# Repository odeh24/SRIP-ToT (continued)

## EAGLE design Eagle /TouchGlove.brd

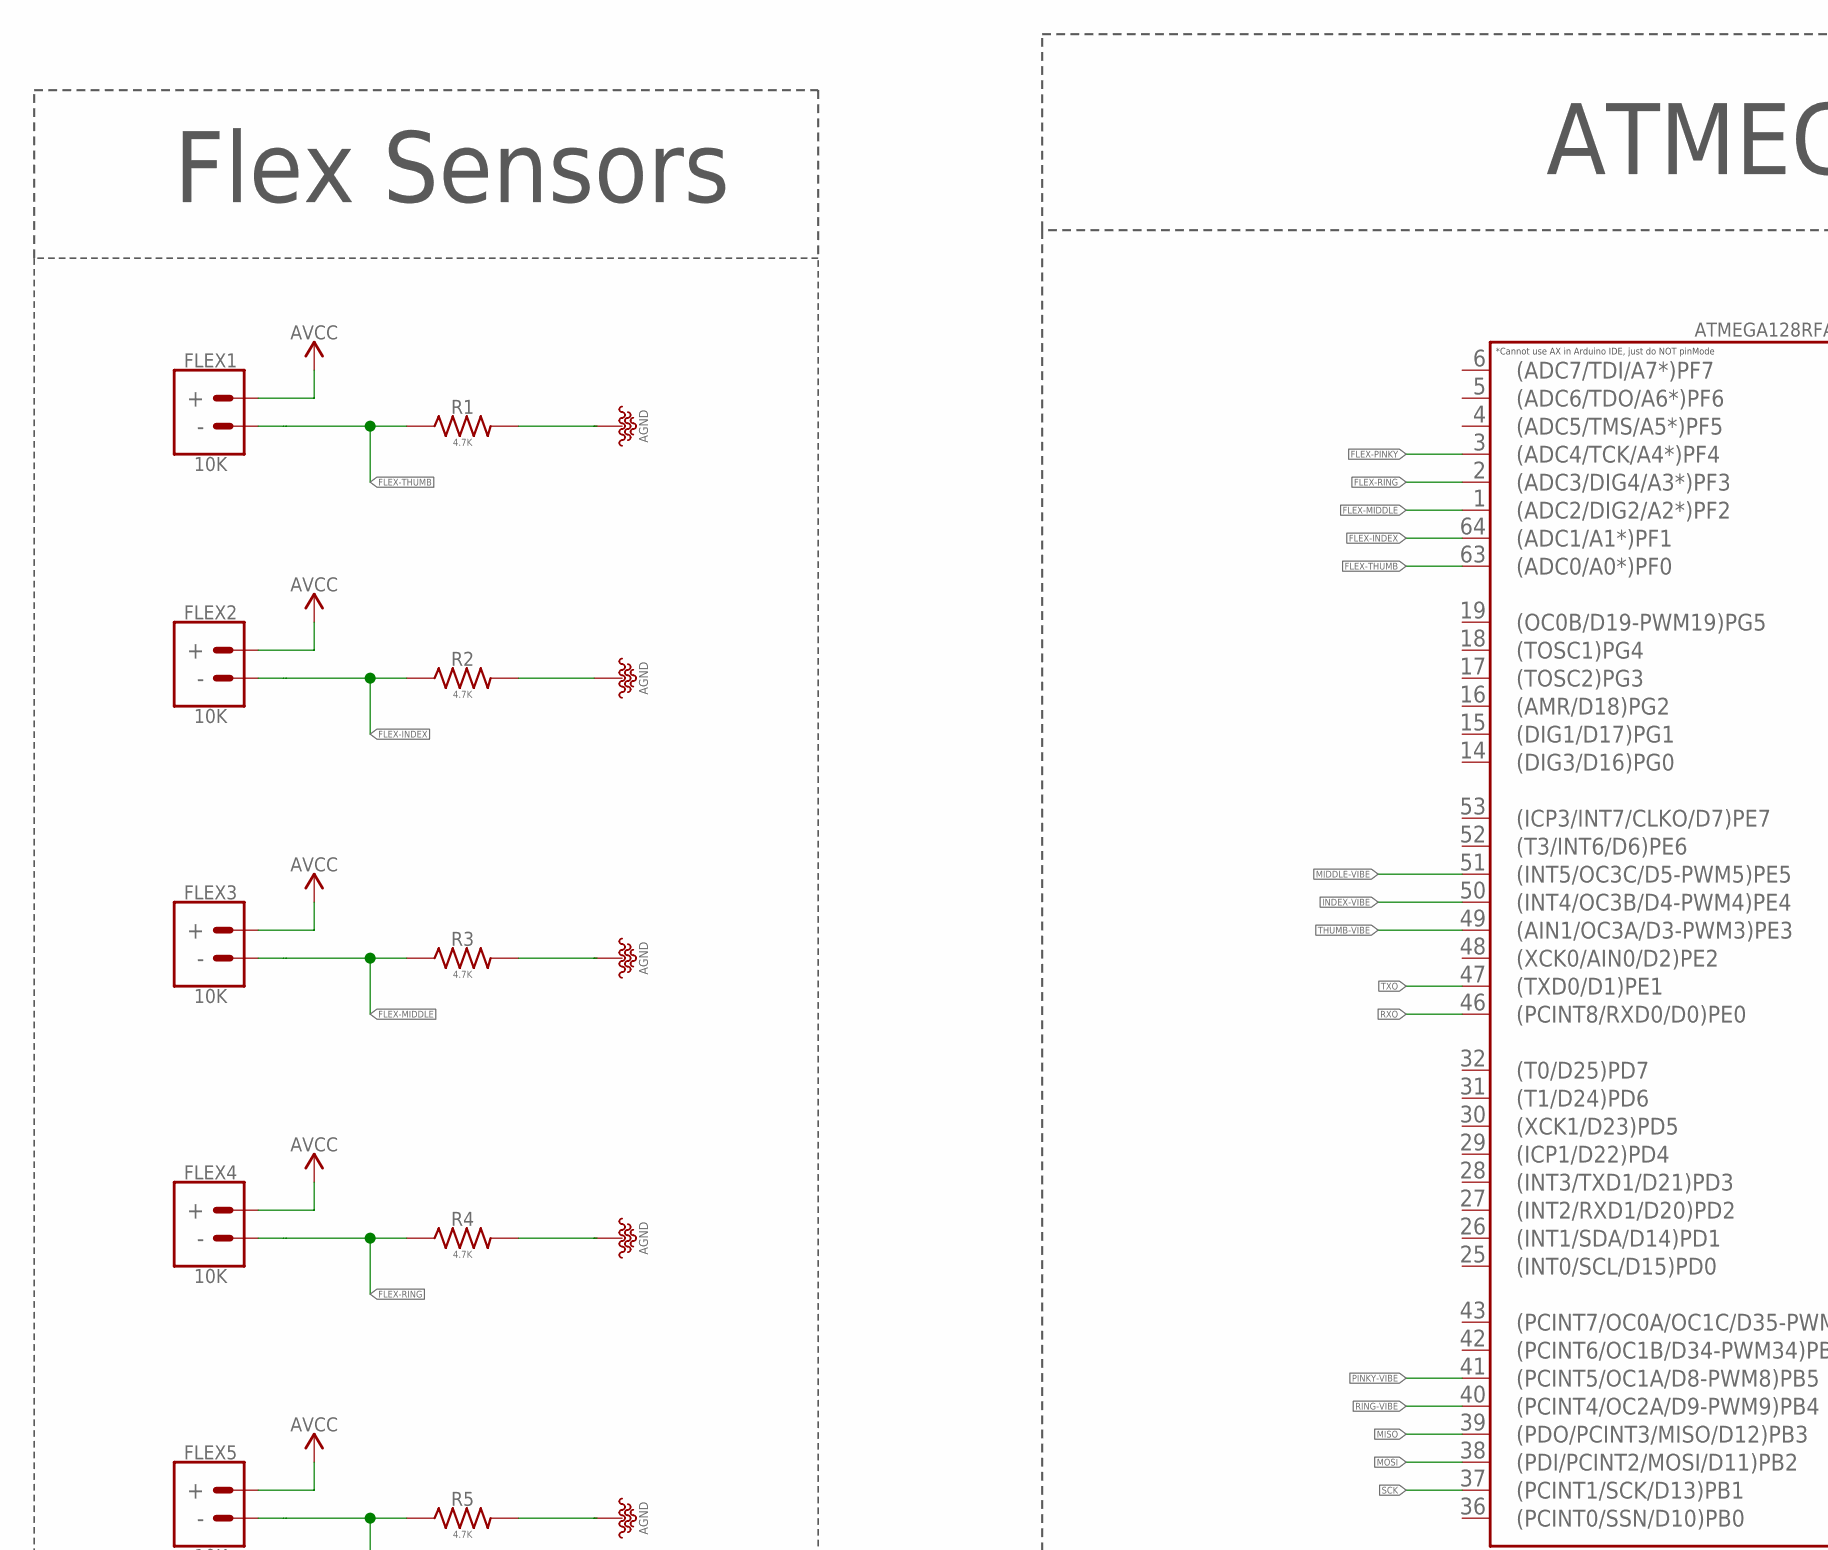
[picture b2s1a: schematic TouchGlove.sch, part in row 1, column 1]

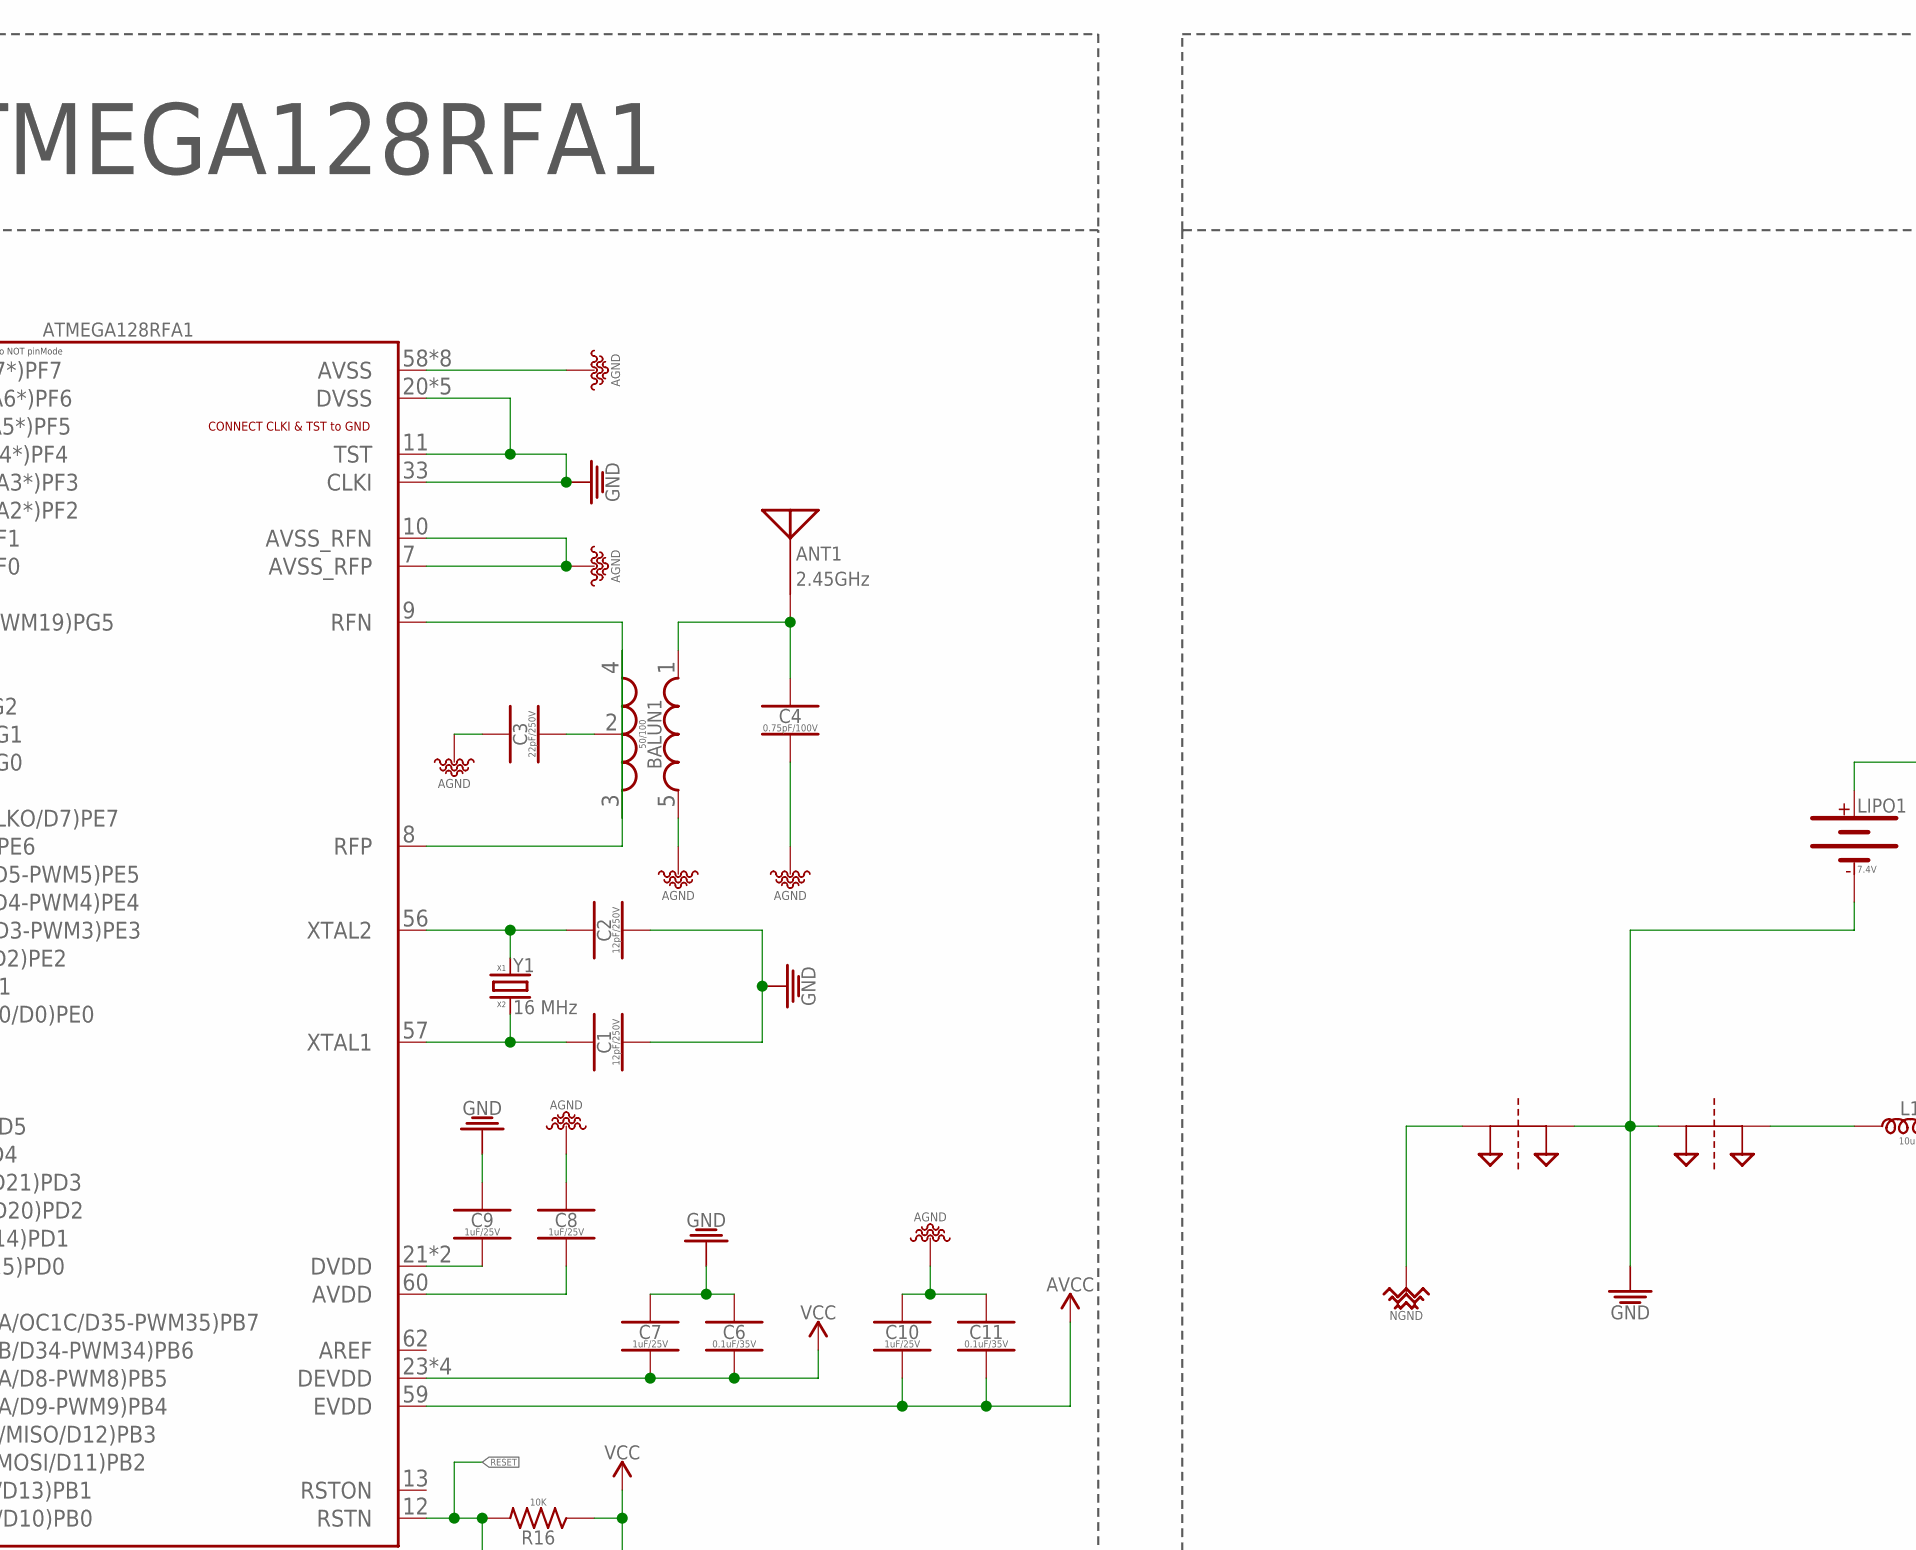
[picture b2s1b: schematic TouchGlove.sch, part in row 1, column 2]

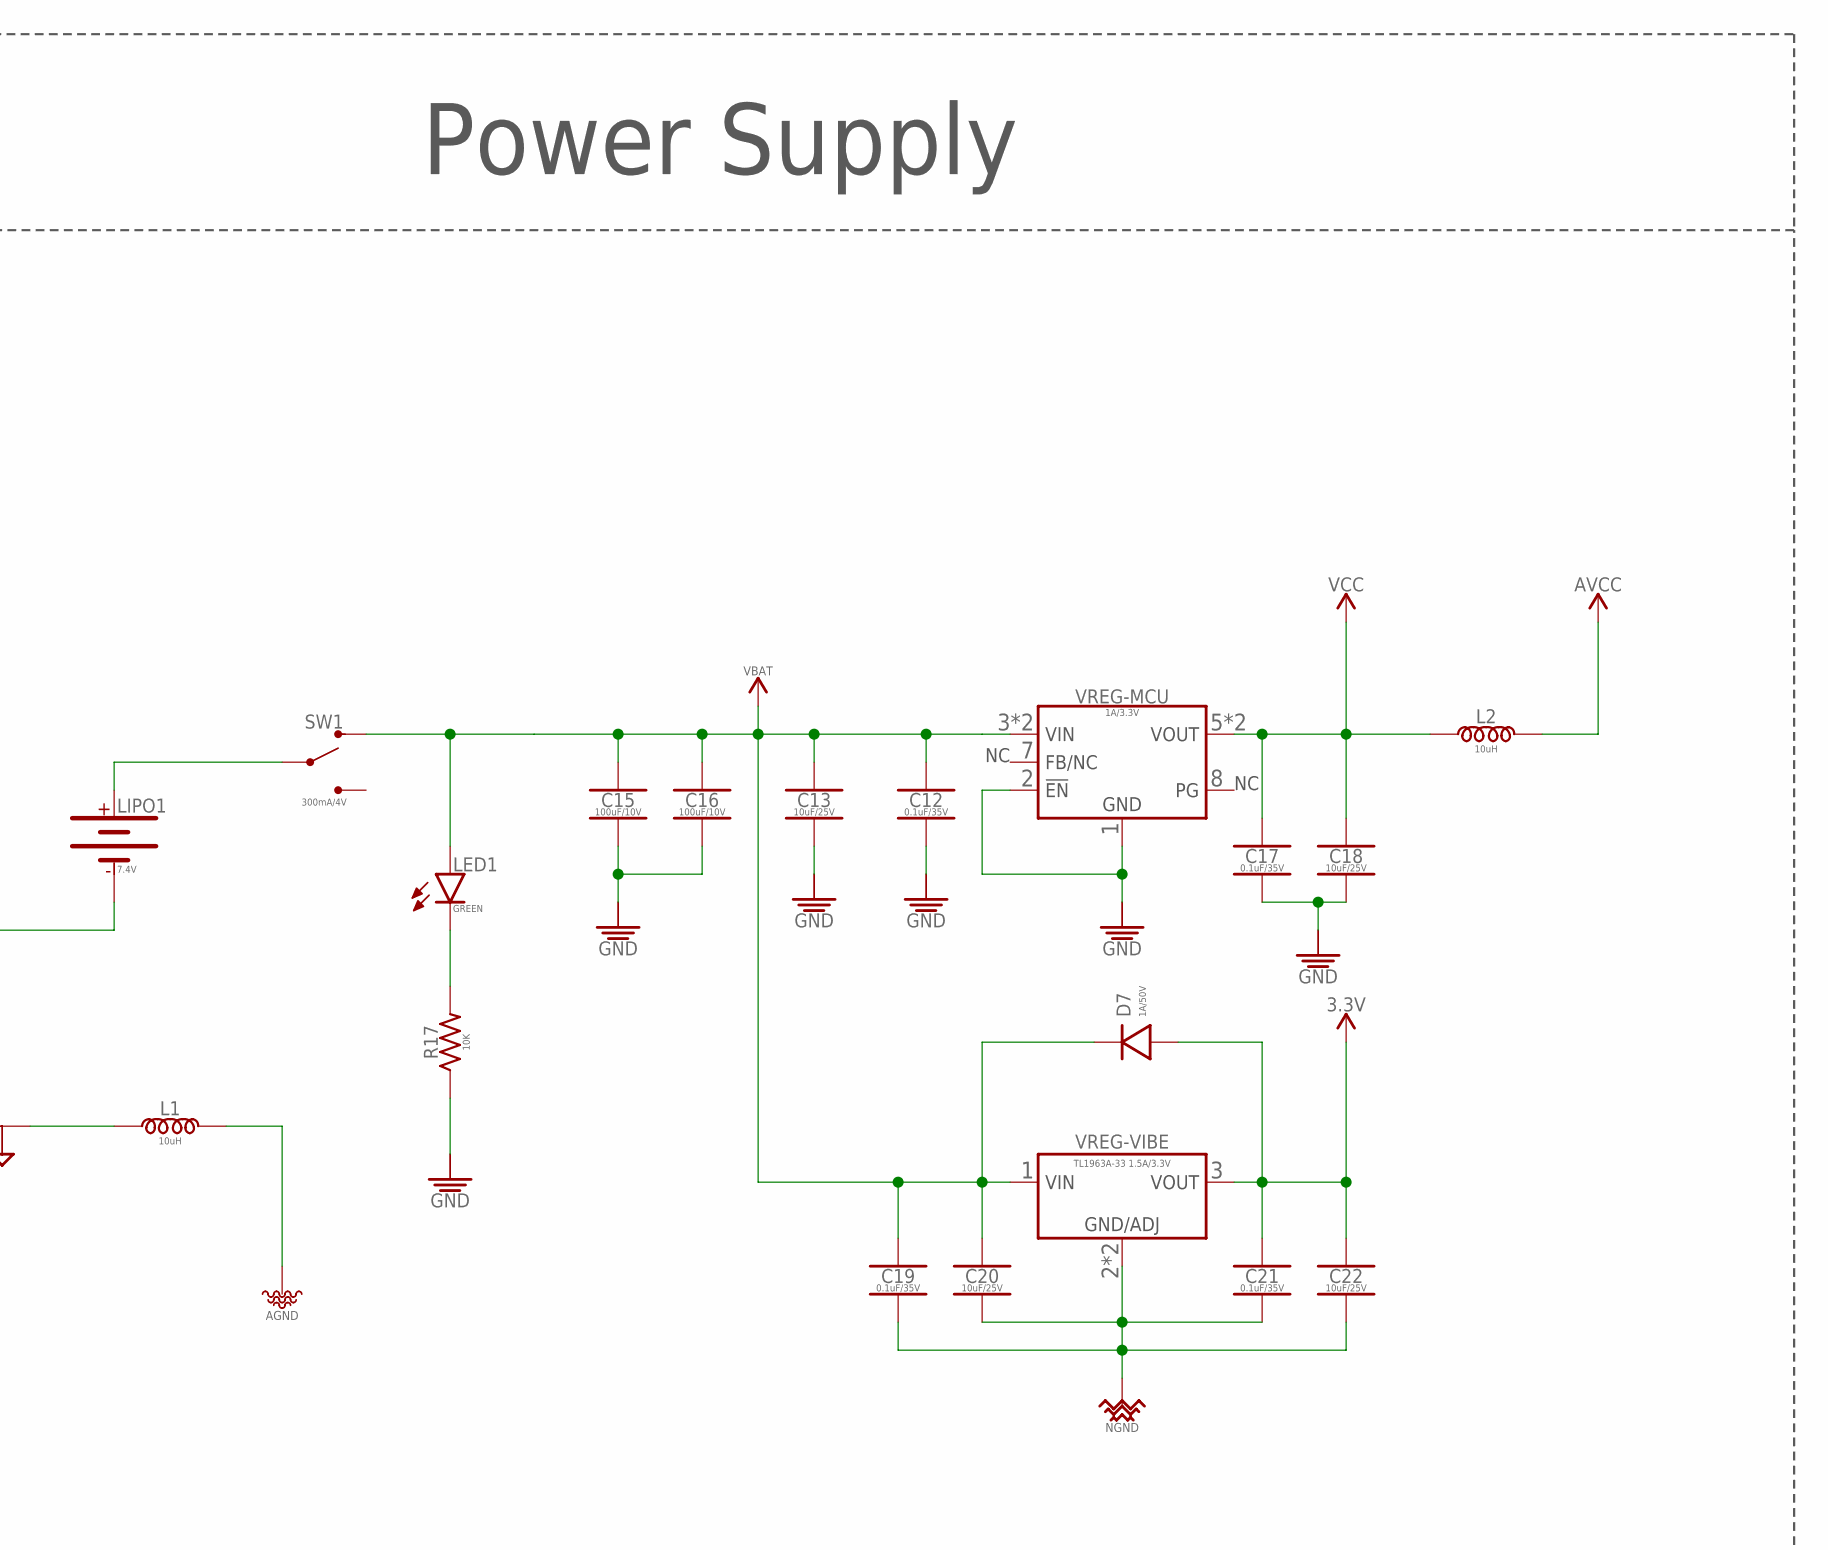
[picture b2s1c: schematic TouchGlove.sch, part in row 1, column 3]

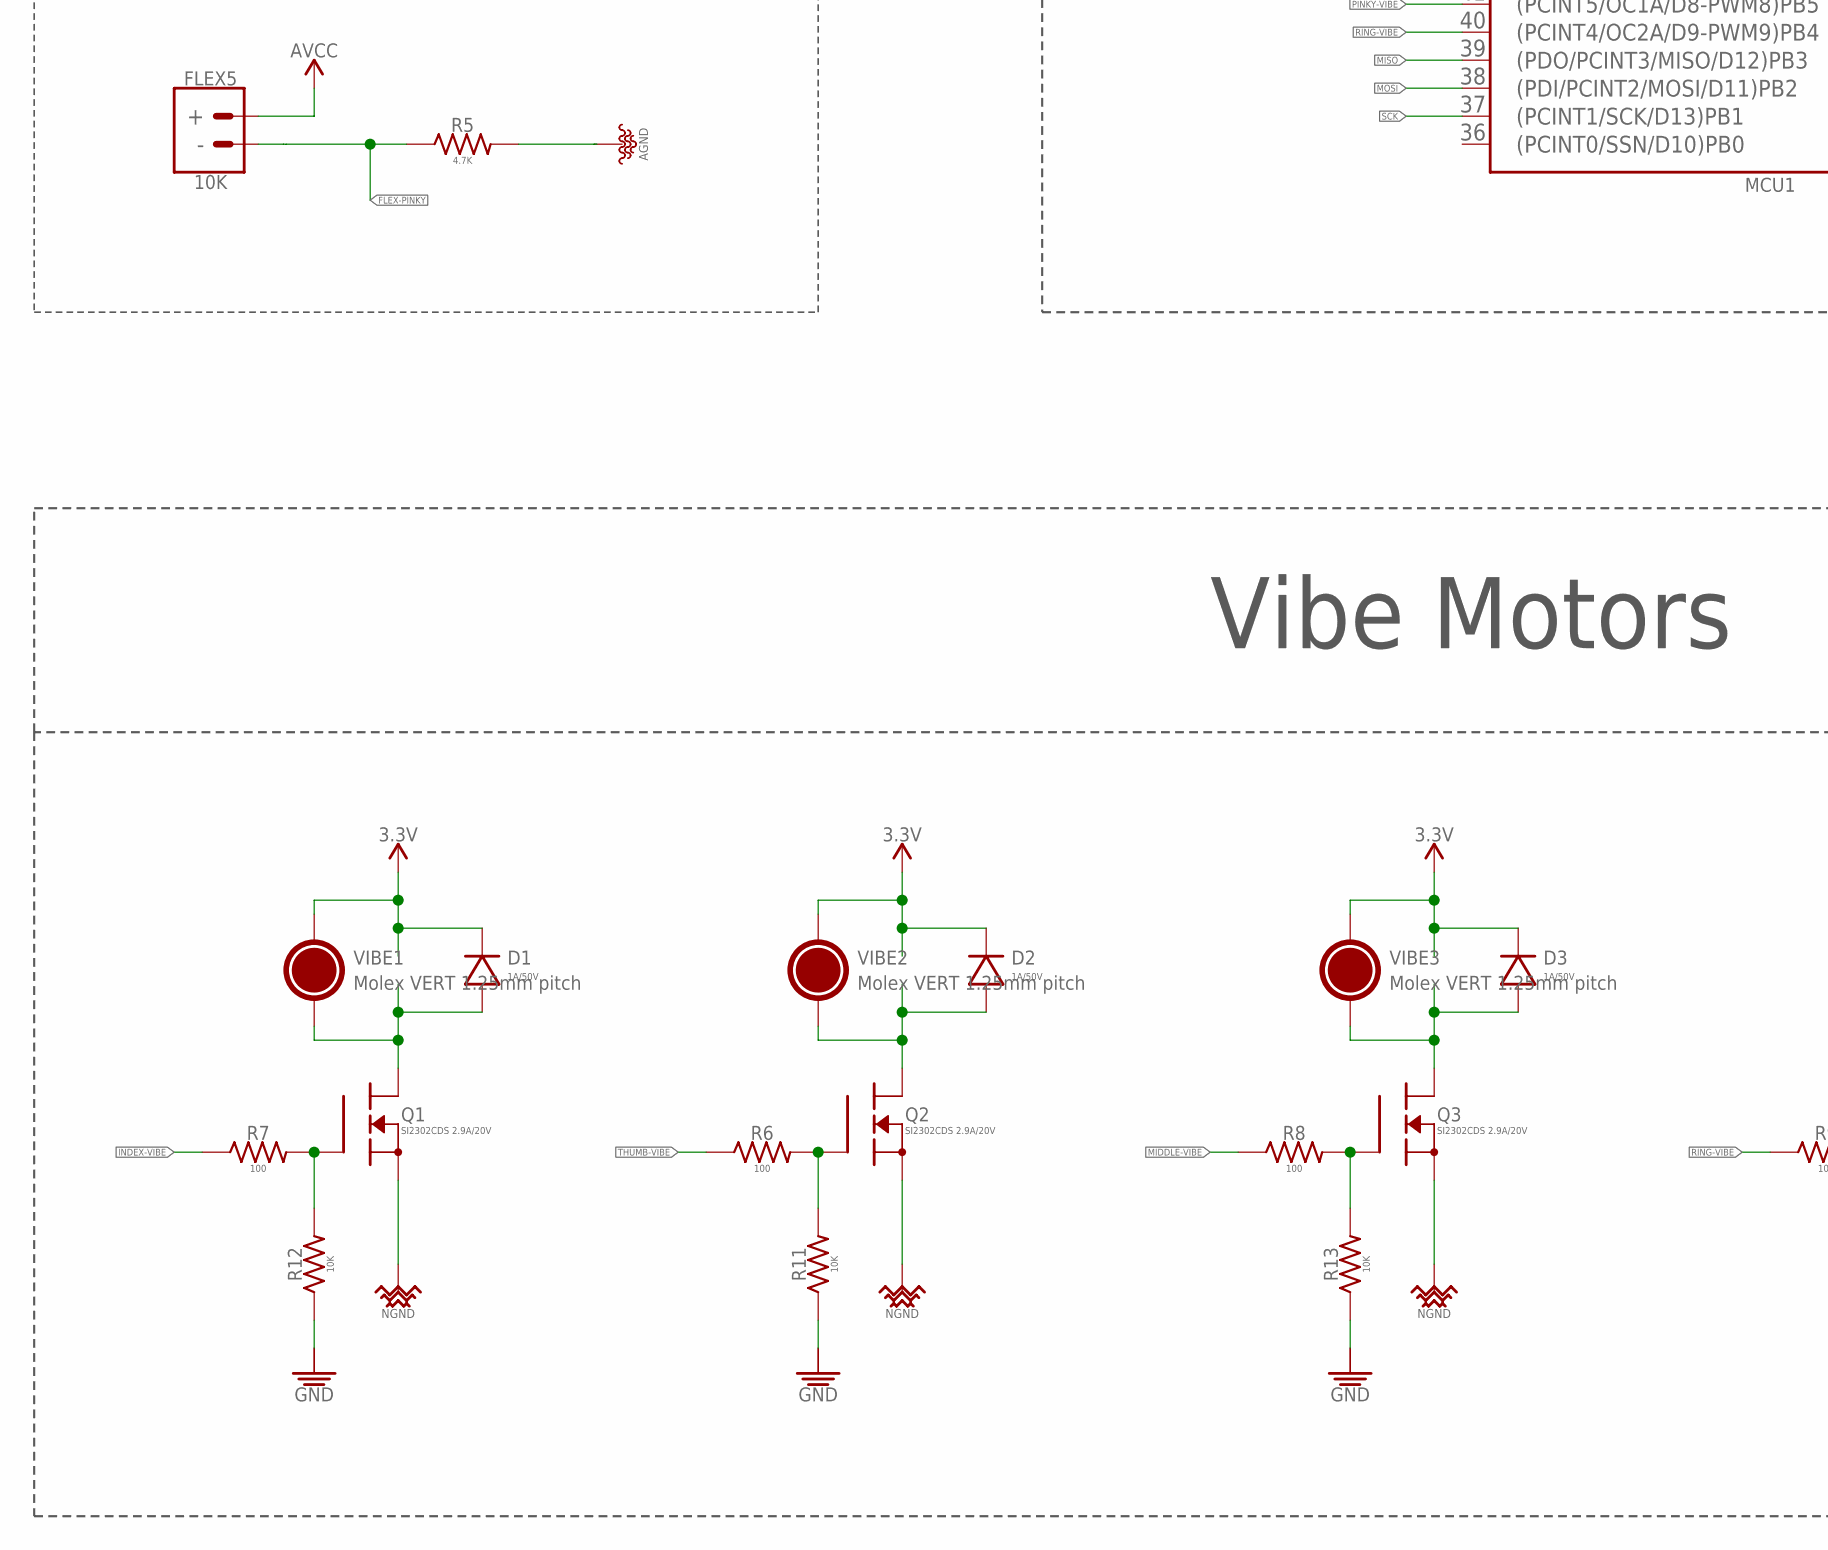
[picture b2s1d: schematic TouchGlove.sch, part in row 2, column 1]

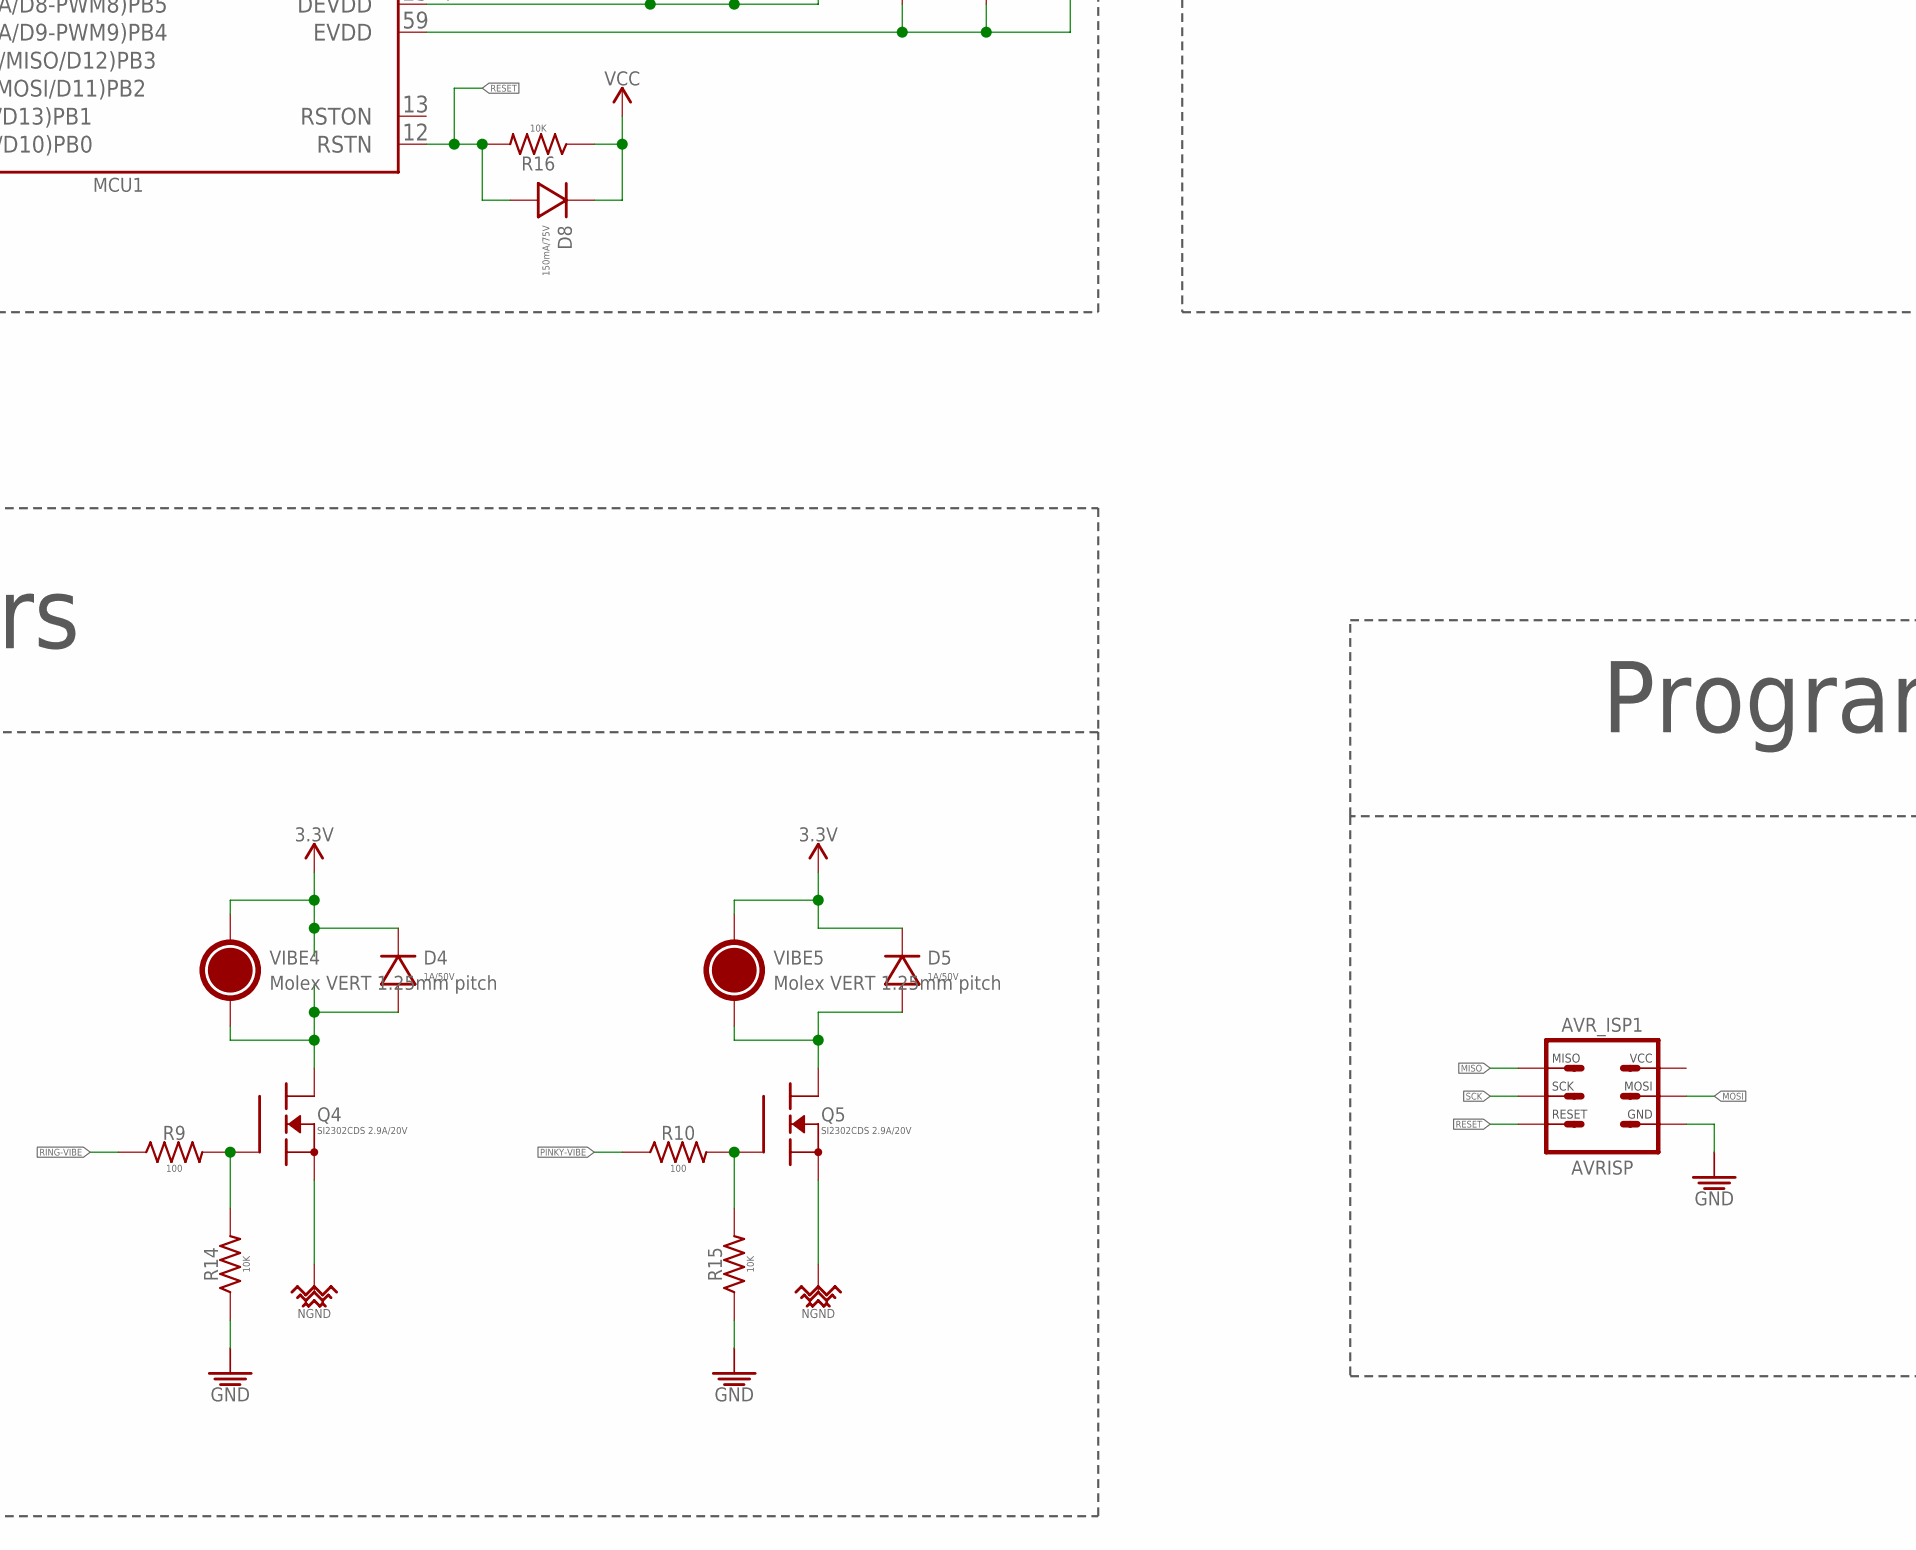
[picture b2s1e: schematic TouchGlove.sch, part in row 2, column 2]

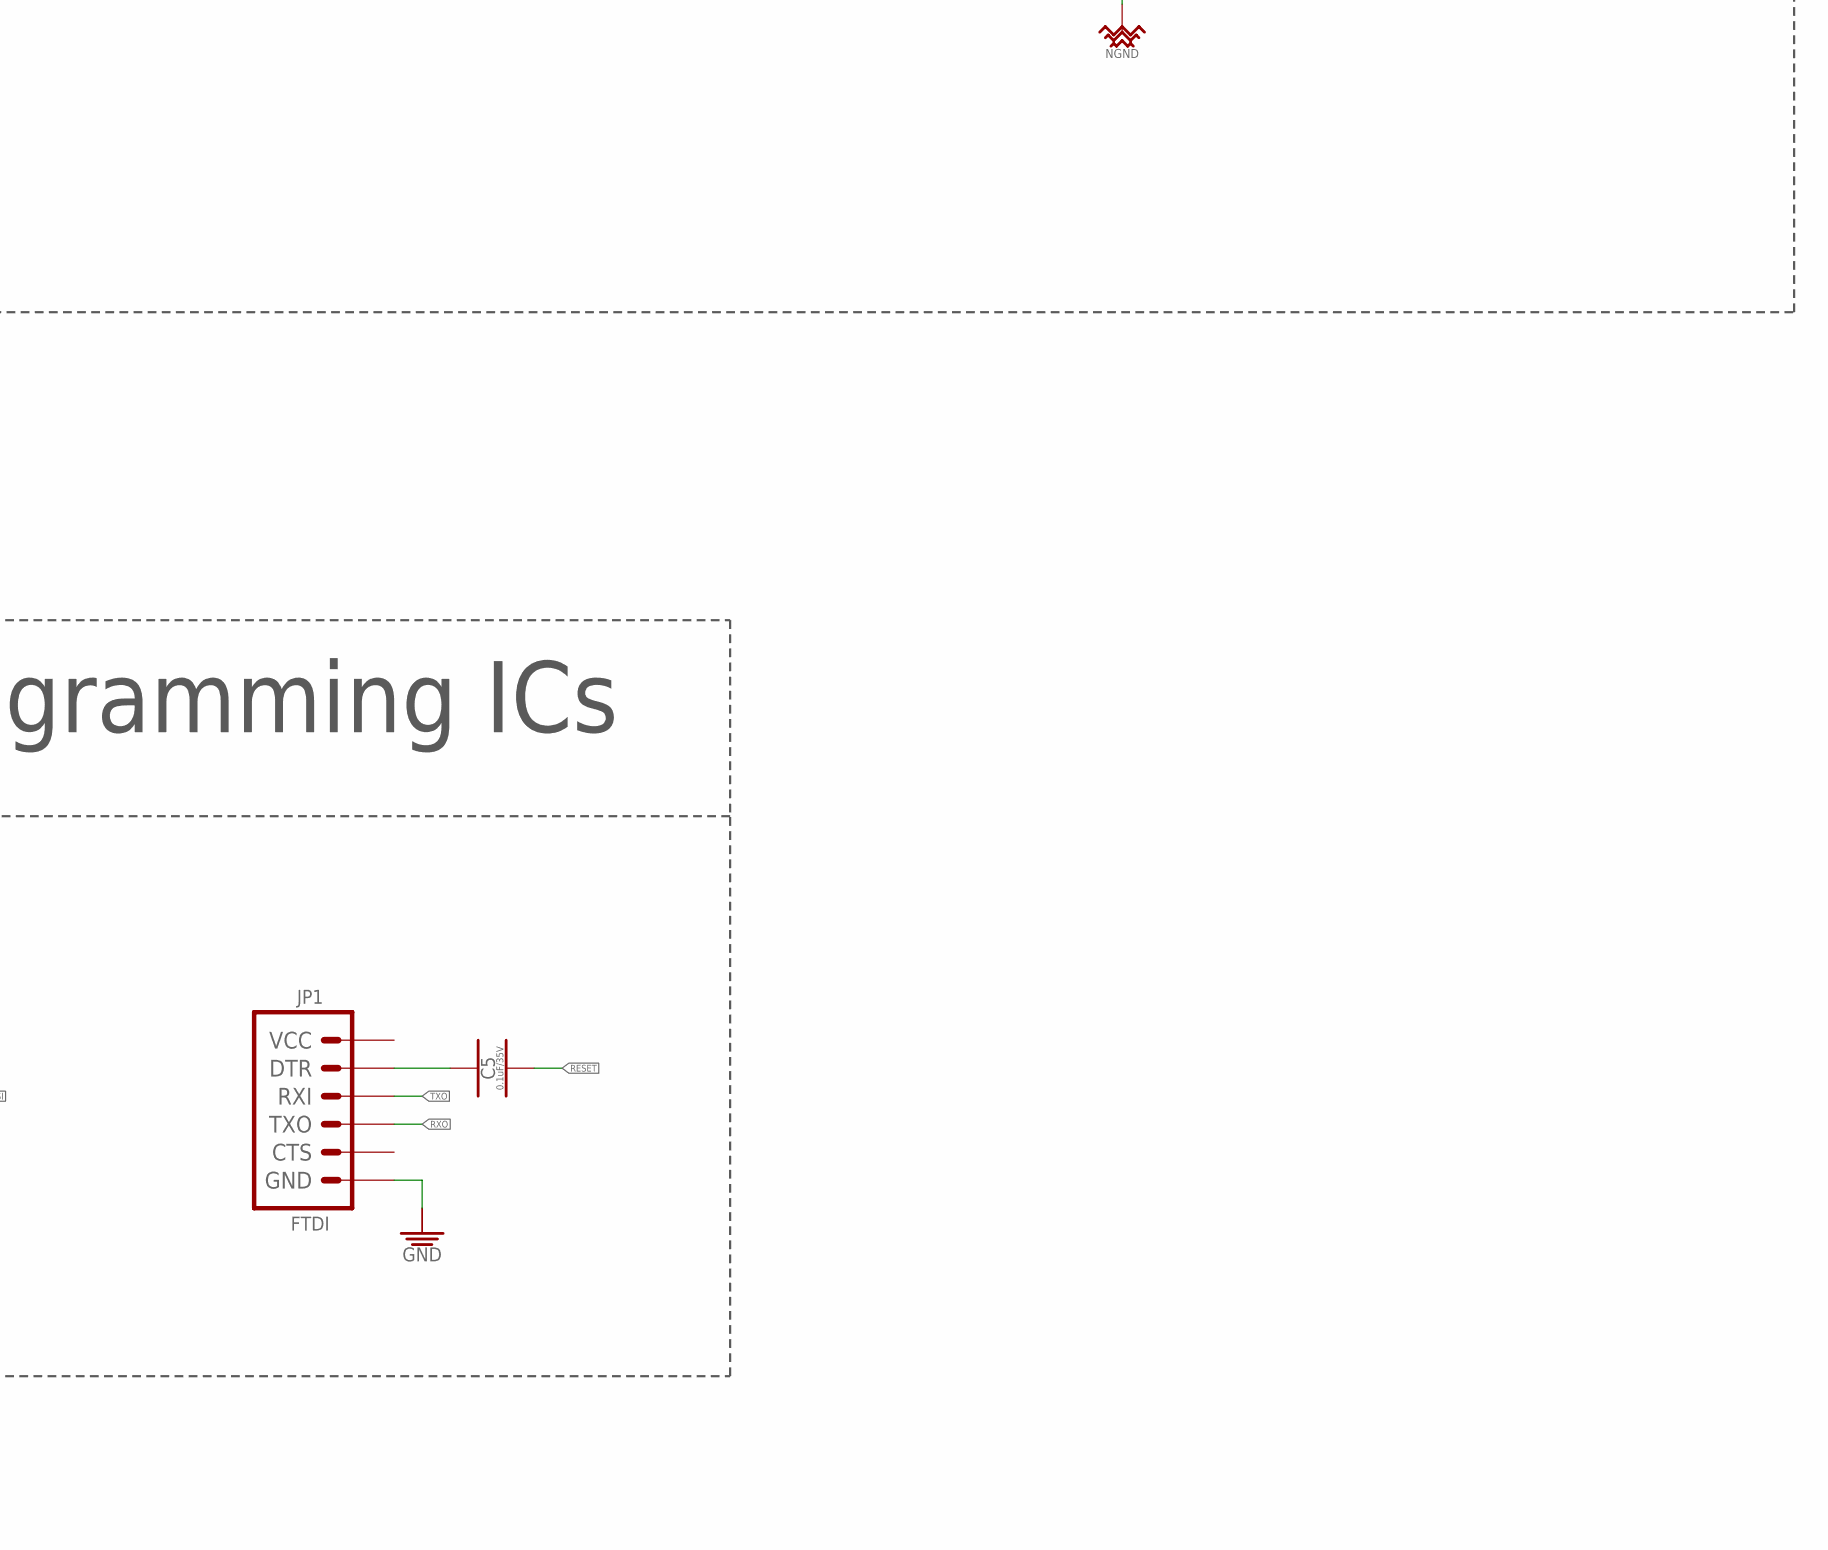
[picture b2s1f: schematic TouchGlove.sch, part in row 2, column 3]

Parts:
ANT1: 2.45GHz; ANTC6522X100
AVR_ISP1: AVRISP; 2X3-NS
BALUN1: 50/100; RESCAXE65P200X125X95-6
C1, C2: 12pF/250V; CAPC2012X95_SMD-0805
C3: 22pF/250V; CAPC2012X95_SMD-0805
C4: 0.75pF/100V; CAPC2012X95_SMD-0805
C5, C6, C11, C12, C17, C19, C21: 0.1uF/35V; CAPC2012X95_SMD-0805
C7, C8, C9, C10: 1uF/25V; CAPC2012X95_SMD-0805
C13, C18, C20, C22: 10uF/25V; CAPC2012X95_SMD-0805
C15, C16: 100uF/10V; CAPC3225X270_SMD-1210
D1, D2, D3, D4, D5, D7: 1A/50V; SODFL3516X170
D8: 150mA/75V; DFN100X60X55-2
FLEX1, FLEX2, FLEX3, FLEX4, FLEX5: 10K; _MOLEX-0530470210_VERT_PITCH-1.25MM
JP1: FTDI; FTDI_BASIC-6PIN-MALE-RA
L1, L2: 10uH; INDC2012X145
LED1: GREEN; LEDC2012X120_LED-0805
LIPO1: 7.4V; BATTERY_MOLEX-89401_RA_PITCH-2MM
MCU1: ATMEGA128RFA1; QFN50P900X900X90-64
Q1, Q2, Q3, Q4, Q5: SI2302CDS 2.9A/20V; SOT95P287X112-3
R1, R2, R3, R4, R5: 4.7K; RESC2012X60_SMD-0805
R6, R7, R8, R9, R10: 100; RESC2012X60_SMD-0805
R11, R12, R13, R14, R15, R16, R17: 10K; RESC2012X60_SMD-0805
SUPPLY38, SUPPLY39: 2PT_GND_TIE
SW1: 300mA/4V; SW_SLIDE_SPDT_RA_SMD_4V_300MA_6.7L-2.6W
VIBE1, VIBE2, VIBE3, VIBE4, VIBE5: Molex VERT 1.25mm pitch; _MOLEX-0530470210_VERT_PITCH-1.25MM
VREG-MCU: 1A/3.3V; SOIC127P600X265-8
VREG-VIBE: TL1963A-33 1.5A/3.3V; SOT229P700X180-4
Y1: 16 MHz; OSCCC500X320X110

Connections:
3.3V: C21.1, C22.1, D1.K, D2.K, D3.K, D4.K, D5.K, D7.A, VIBE1.1 (+), VIBE2.1 (+), VIBE3.1 (+), VIBE4.1 (+), VIBE5.1 (+), VREG-VIBE.3 (VO)
AGND: BALUN1.5 (GND), C3.1, C4.2, C8.1, C10.1, C11.1, L1.2, MCU1.7 (AVSS_RFP), MCU1.10 (AVSS_RFN), MCU1.58 (AVSS), MCU1.61 (AVSS), MCU1.EP (AVSS), MCU1.P$1 (AVSS), MCU1.P$2 (AVSS), MCU1.P$3 (AVSS), MCU1.P$4 (AVSS), MCU1.P$5 (AVSS), R1.2, R2.2, R3.2, R4.2, R5.2
AVCC: C10.2, C11.2, FLEX1.1 (+), FLEX2.1 (+), FLEX3.1 (+), FLEX4.1 (+), FLEX5.1 (+), L2.2, MCU1.59 (EVDD)
FLEX-INDEX: FLEX2.2 (-), MCU1.64 ((ADC1/A1*)PF1), R2.1
FLEX-MIDDLE: FLEX3.2 (-), MCU1.1 ((ADC2/DIG2/A2*)PF2), R3.1
FLEX-PINKY: FLEX5.2 (-), MCU1.3 ((ADC4/TCK/A4*)PF4), R5.1
FLEX-RING: FLEX4.2 (-), MCU1.2 ((ADC3/DIG4/A3*)PF3), R4.1
FLEX-THUMB: FLEX1.2 (-), MCU1.63 ((ADC0/A0*)PF0), R1.1
GND: AVR_ISP1.GND, C1.2, C2.2, C6.1, C7.1, C9.1, C12.2, C13.2, C15.2, C16.2, C17.2, C18.2, JP1.GND, LIPO1.-, MCU1.11 (TST), MCU1.20 (DVSS), MCU1.24 (DVSS), MCU1.33 (CLKI), MCU1.35 (DVSS), MCU1.45 (DVSS), MCU1.55 (DVSS), R11.1, R12.1, R13.1, R14.1, R15.1, R17.1, SUPPLY38.P$2, SUPPLY39.P$1, VREG-MCU.1 (GND), VREG-MCU.2 (!EN)
INDEX-VIBE: MCU1.50 ((INT4/OC3B/D4-PWM4)PE4), R7.1
MIDDLE-VIBE: MCU1.51 ((INT5/OC3C/D5-PWM5)PE5), R8.1
MISO: AVR_ISP1.MISO, MCU1.39 ((PDO/PCINT3/MISO/D12)PB3)
MOSI: AVR_ISP1.MOSI, MCU1.38 ((PDI/PCINT2/MOSI/D11)PB2)
unnamed: D1.A, Q1.3 (D), VIBE1.2 (-)
unnamed: D2.A, Q2.3 (D), VIBE2.2 (-)
unnamed: D3.A, Q3.3 (D), VIBE3.2 (-)
unnamed: D4.A, Q4.3 (D), VIBE4.2 (-)
unnamed: D5.A, Q5.3 (D), VIBE5.2 (-)
unnamed: C2.1, MCU1.56 (XTAL2), Y1.1 (XTAL1)
unnamed: C1.1, MCU1.57 (XTAL1), Y1.3 (XTAL2)
unnamed: BALUN1.2 (GND), C3.2
unnamed: ANT1.1, BALUN1.1 (IN), C4.1
unnamed: BALUN1.3 (OUT1), MCU1.9 (RFN)
unnamed: BALUN1.4 (OUT2), MCU1.8 (RFP)
unnamed: C5.1, JP1.DTR
unnamed: Q2.1 (G), R6.2, R11.2
unnamed: LIPO1.+, SW1.2
unnamed: Q1.1 (G), R7.2, R12.2
unnamed: Q3.1 (G), R8.2, R13.2
unnamed: L1.1, SUPPLY39.P$2
unnamed: Q4.1 (G), R9.2, R14.2
unnamed: C8.2, MCU1.60 (AVDD)
unnamed: Q5.1 (G), R10.2, R15.2
unnamed: C9.2, MCU1.21 (DVDD), MCU1.22 (DVDD)
unnamed: LED1.K, R17.2
NGND: C19.2, C20.2, C21.2, C22.2, Q1.2 (S), Q2.2 (S), Q3.2 (S), Q4.2 (S), Q5.2 (S), SUPPLY38.P$1, VREG-VIBE.2 (GND), VREG-VIBE.4 (GND)
PINKY-VIBE: MCU1.41 ((PCINT5/OC1A/D8-PWM8)PB5), R10.1
RESET: AVR_ISP1.RESET, C5.2, D8.A, MCU1.12 (RSTN), R16.2
RING-VIBE: MCU1.40 ((PCINT4/OC2A/D9-PWM9)PB4), R9.1
RXO: JP1.TXO, MCU1.46 ((PCINT8/RXD0/D0)PE0)
SCK: AVR_ISP1.SCK, MCU1.37 ((PCINT1/SCK/D13)PB1)
THUMB-VIBE: MCU1.49 ((AIN1/OC3A/D3-PWM3)PE3), R6.1
TXO: JP1.RXI, MCU1.47 ((TXD0/D1)PE1)
VBAT: C12.1, C13.1, C15.1, C16.1, C19.1, C20.1, D7.K, LED1.A, SW1.1 (S1), VREG-MCU.3 (VIN), VREG-MCU.4 (VIN), VREG-VIBE.1 (VI)
VCC: C6.2, C7.2, C17.1, C18.1, D8.K, L2.1, MCU1.23 (DEVDD), MCU1.34 (DEVDD), MCU1.44 (DEVDD), MCU1.54 (DEVDD), R16.1, VREG-MCU.5 (VOUT), VREG-MCU.6 (VOUT)

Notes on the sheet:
Flex Sensors
Programming ICs
Vibe Motors
ATMEGA128RFA1
Power Supply

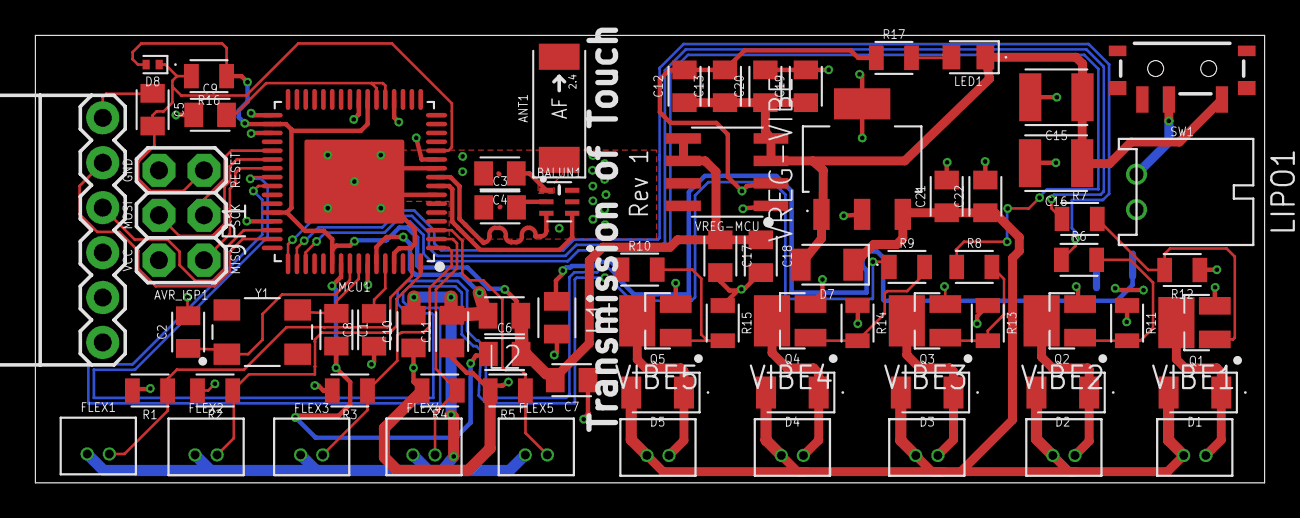
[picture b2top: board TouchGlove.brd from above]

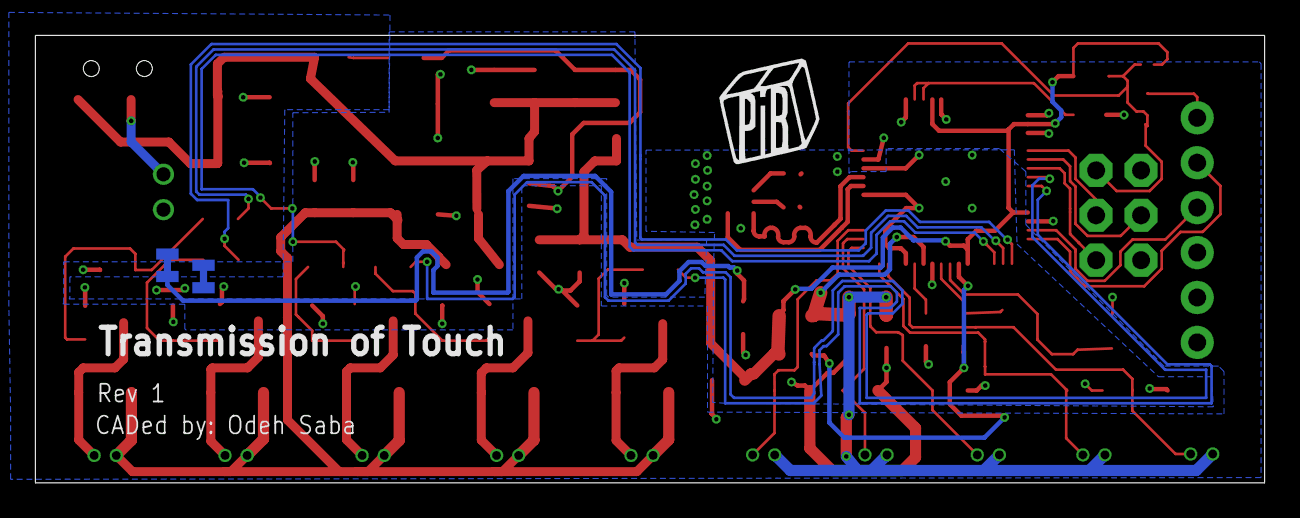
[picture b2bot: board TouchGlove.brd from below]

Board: 2 copper layers, 69.5 x 25.3 mm, 76 parts (3 on the bottom side), 45 nets.

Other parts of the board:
U$1: PIB_LOGO_10MM

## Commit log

2018-07-09 First commit adding all up to date testing code
2018-07-10 Hopefully this works!
2018-07-10 Add unified TouchGlove and Robotic Arm code
2018-07-10 Reworked code
2018-07-10 The vibe motors work well!
2018-07-11 Now with the Eagle Schematic
2018-07-11 Eagle folder added and named so
2018-07-11 Reorganizeing directories and files
2018-07-13 Update to eagle schematics, barebones of glove and arm board schematics complete
2018-07-19 Updated RobotArm Schematic
2018-07-19 Added so many capacitors it's not even funny
2018-07-31 I routed everything except for VCC. I am not sure how to proceed from here.
2018-08-01 last update
2018-08-01 Massaged around some stuff.
2018-08-02 Adding finished touch glove schematic and pcb board
2018-08-03 reorganized
2018-08-03 Fixing DRC errors in touchglove brd
2018-08-03 Hopefully not too much to change
2018-08-03 jesus help me
2018-08-03 Rotated that shitty chip.
2018-08-03 Add .gitignore.
2018-08-03 Remove swap files.
2018-08-03 Create antenna CKTry.
2018-08-03 thank you so much Colin!
2018-08-03 Fixing very large amount of bugs in touch glove schematic
2018-08-03 Please check changes and order this piece
2018-08-07 attempt at update
2018-08-07 test
2018-08-07 deleted arm schematic
2018-08-07 Reorganized eagle into one folder
2018-08-08 Revert to 8e7366f when I asked Colin to order
2018-08-08 Rev 1: Ready for fab.
2018-08-08 Add gitignore file
2018-08-09 ruh roh.....
2018-08-09 Remove that shit.
2018-08-09 Remove DS_Store shit.
2018-08-09 Remove the swap files.
